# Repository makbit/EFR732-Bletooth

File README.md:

# EFR732-Bluetooth
EFR732 - is a multi-protocol radio board based on the [EFR32MG1P732F256GM32 @40MHz MCU](https://www.silabs.com/wireless/zigbee/efr32mg1-series-1-socs/device.efr32mg1p732f256gm32) from the SiliconLabs in the 5x5mm QFN32 package. Now this MCU is announced as deprecated. :disappointed:

This MCU supports:
* Bluetooth Smart (BLE),
* ZigBee,
* Thread,
* Proprietary protocols.

Maximum TX Power is: 2.4 GHz @ 19.5 dBm, Antenna in the SMA connector adds +3dBm.
This MCU integrate a 512kB serial flash in the package.

### Key features:
 - The board has JTAG/SWD pins compatible with the J-Link debug adapter (PF0 - SWCLK, PF1 - SWDIO, PF2 - SWO).
 - The on-board microphone with the amplifier is connected to the MCU ADC port (PB13).
 - The iDAC output is amplified with the LM321 (PB12).
 - There is a USB-to-UART bridge based on the [EFM8UB31F40 MCU](https://www.silabs.com/mcu/8-bit/efm8-universal-bee/device.efm8ub31f40g-qsop24) : P04_TX -> PA1_RX, P05_RX -> PA0_TX. I hope this 8051 MCU can be used as a programmer/debugger someday.
 - Two pins are connected: P03 -> PB11 (clk), P06 -> PD13 (cs). Debug pins are not connected yet.
 - User push-button is connected to PF3.

The [`Hardware`](Hardware) folder contains Eagle CAD 9.0 schematics files. Component library can be found in my repositories.
The board schematics can be found in the[`Hardware/EFR732.png`](Hardware/EFR732.png) file.

### TODO
- [ ] Add firmware folder with examples and some useful stuff.
- [ ] Write USB-to-UART firmware for EFM8.

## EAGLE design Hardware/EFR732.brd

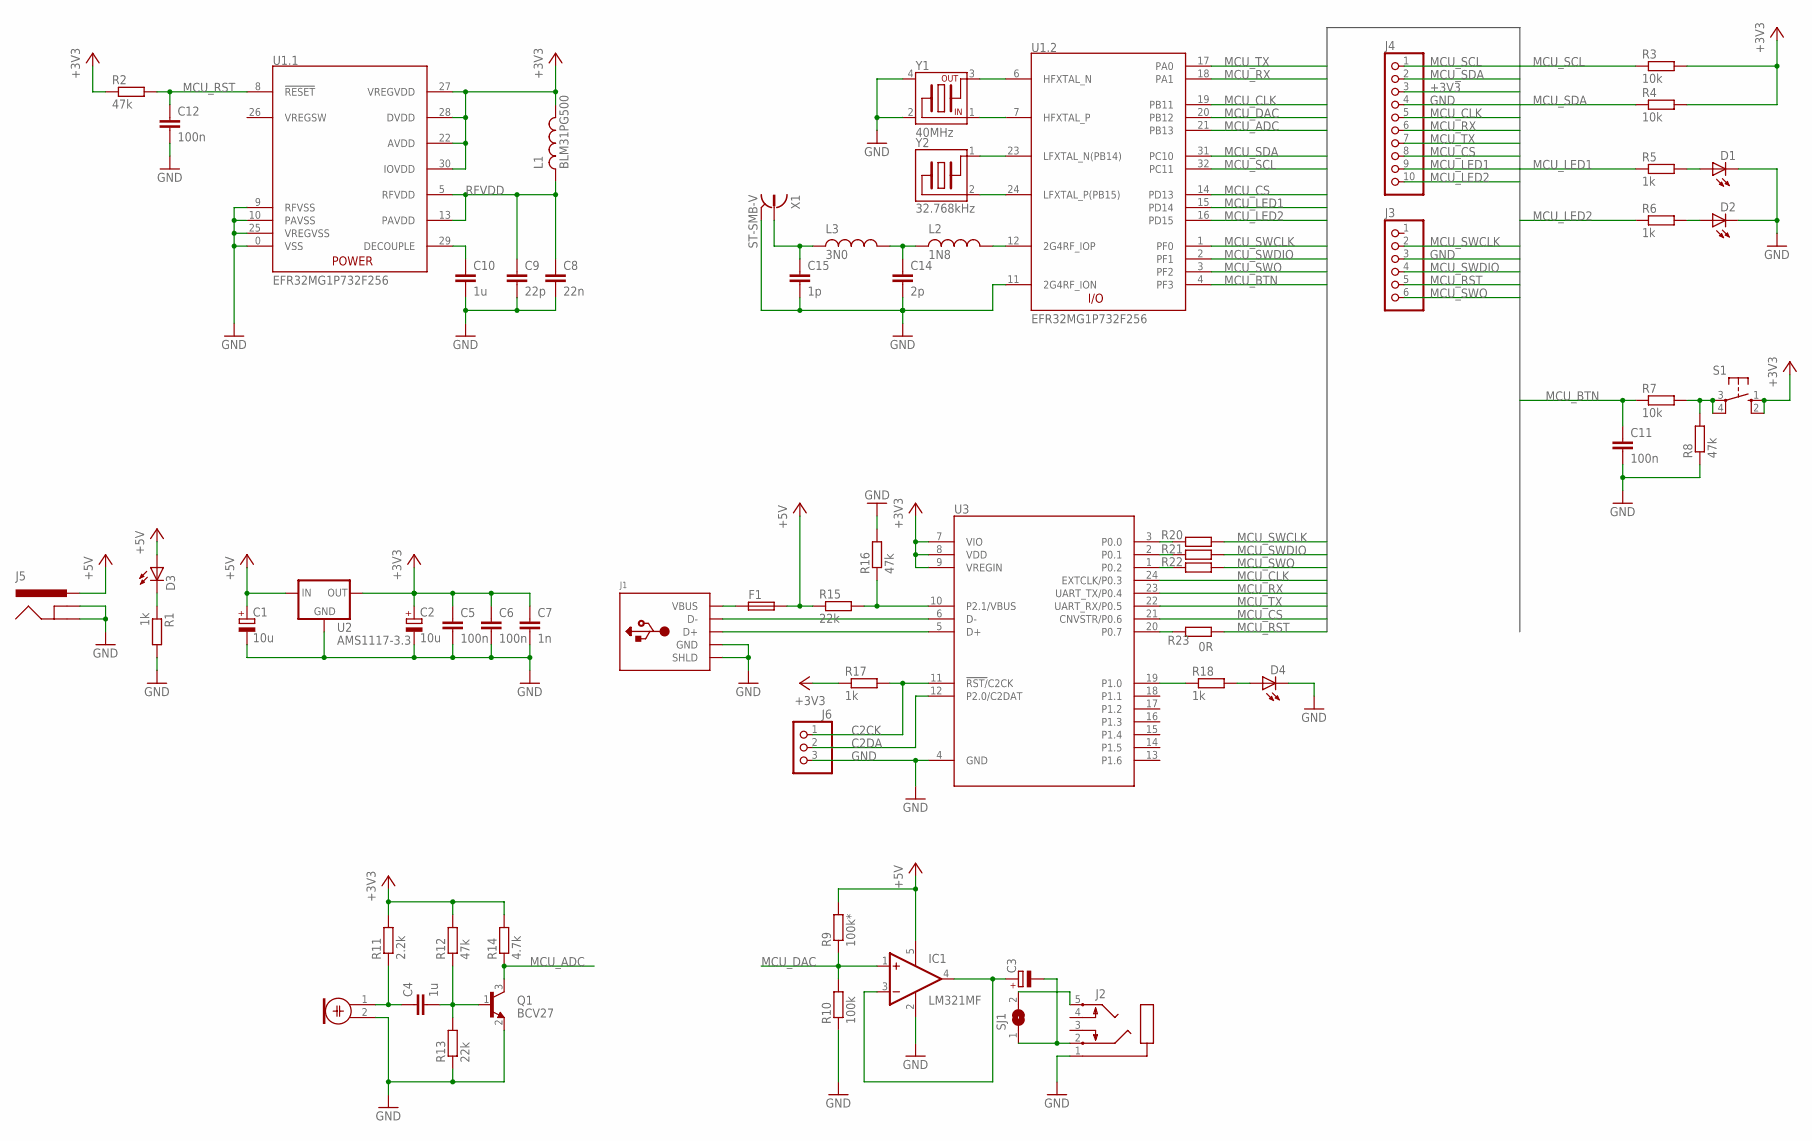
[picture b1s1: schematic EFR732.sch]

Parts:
C1, C2: 10u; RCL-1206F-POL
C3: CPOL-EU; RCL-1206F-POL
C4, C10: 1u; RCL-1206F
C5, C6, C11, C12: 100n; RCL-0805F
C7: 1n; RCL-0805F
C8: 22n; RCL-0805F
C9: 22p; RCL-0805F
C14: 2p; RCL-0805F
C15: 1p; RCL-0805F
D1, D2, D3, D4: LED1206; LED-1206F
F1: FUSE-NSMF; RCL-1206F
IC1: LM321MF; SOT23-5
J1: USB-TYPE-B; USB-TYPE-B-4P
J2: AUDIO-JACK-3.5MM; AUDIO-PG203J
J3: PINH-1X06
J4: PINH-1X10
J5: POWER_JACK; POWER_JACK_PTH
J6: PINHD-1X3; 1X03
L1: BLM31PG500; RCL-1206F
L2: 1N8; RCL-0603F
L3: 3N0; RCL-0603F
M1: ELECTRET_MICROPHON-WM-62PC/62PK; WM-62PC/62PK
Q1: BCV27; SOT23
R1, R5, R6, R17, R18: 1k; RCL-0805F
R2, R8, R12, R16: 47k; RCL-0805F
R3, R4, R7: 10k; RCL-0805F
R9: 100k*; RCL-0805F
R10: 100k; RCL-0805F
R11: 2.2k; RCL-0805F
R13, R15: 22k; RCL-0805F
R14: 4.7k; RCL-0805F
R20, R21, R22: R-EU0805; RCL-0805F
R23: 0R; RCL-0805F
S1: SWITCH-10-XX; BUTTON-B3F-10XX
SJ1: SJ
U1: EFR32MG1P732F256; QFN32_5X5MM_EFR32MG1
U2: AMS1117-3.3; SOT223
U3: EFM8UB31F40G-QSOP24; QSOP24-3.9X8.65MM
X1: ST-SMB-V
Y1: 40MHz; XTAL-FA-238
Y2: 32.768kHz; XTAL-FC-135

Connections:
+3V3: C2.+, C5.1, C6.1, C7.1, J4.3, L1.2, R2.1, R3.2, R4.2, R11.2, R12.2, R14.2, R17.1, S1.1 (S), S1.2 (S1), U1.22 (AVDD), U1.27 (VREGVDD), U1.28 (DVDD), U1.30 (IOVDD), U2.2 (OUT), U2.4 (OUT), U3.7 (VIO), U3.8 (VDD), U3.9 (VREGIN)
+5V: C1.+, D3.A, F1.2, IC1.5 (V+), J5.PWR, R9.2, R15.1, U2.3 (IN)
C2CK: J6.1, R17.2, U3.11 (!RST/!C2CK)
C2DA: J6.2, U3.12 (P2.0/C2DAT)
GND: C1.-, C2.-, C5.2, C6.2, C7.2, C8.2, C9.2, C10.2, C11.2, C12.2, C14.2, C15.2, D1.C, D2.C, D4.C, IC1.2 (V-), J1.4_GND (GND), J1.M1 (SHLD), J1.M2 (SHLD), J2.1, J3.3, J4.4, J5.GND, J5.GNDBREAK, J6.3, M1.2, Q1.2 (E), R1.2, R8.1, R10.1, R13.1, R16.2, U1.0 (VSS), U1.9 (RFVSS), U1.10 (PAVSS), U1.11 (2G4RF_ION), U1.25 (VREGVSS), U2.1 (GND), U3.4 (GND), X1.2, X1.3 (2), X1.4 (2), X1.5 (2), Y1.2, Y1.4
MCU_ADC: Q1.3 (C), R14.1, U1.21 (PB13)
MCU_BTN: C11.1, R7.1, U1.4 (PF3)
MCU_CLK: J4.5, U1.19 (PB11), U3.24 (EXTCLK/P0.3)
MCU_CS: J4.8, U1.14 (PD13), U3.21 (CNVSTR/P0.6)
MCU_DAC: IC1.1 (+IN), R9.1, R10.2, U1.20 (PB12)
MCU_LED1: J4.9, R5.1, U1.15 (PD14)
MCU_LED2: J4.10, R6.1, U1.16 (PD15)
MCU_RST: C12.1, J3.5, R2.2, R23.2, U1.8 (!RESET)
MCU_RX: J4.6, U1.18 (PA1), U3.23 (UART_TX/P0.4)
MCU_SCL: J4.1, R3.1, U1.32 (PC11)
MCU_SDA: J4.2, R4.1, U1.31 (PC10)
MCU_SWCLK: J3.2, R20.2, U1.1 (PF0)
MCU_SWDIO: J3.4, R21.2, U1.2 (PF1)
MCU_SWO: J3.6, R22.2, U1.3 (PF2)
MCU_TX: J4.7, U1.17 (PA0), U3.22 (UART_RX/P0.5)
unnamed: U1.23 (LFXTAL_N(PB14)), Y2.1 (1.XIN)
unnamed: U1.24 (LFXTAL_P(PB15)), Y2.2 (2.XIN)
unnamed: U1.7 (HFXTAL_P), Y1.1 (X.IN)
unnamed: U1.6 (HFXTAL_N), Y1.3 (X.OUT)
unnamed: F1.1, J1.1_VBUS (VBUS)
unnamed: C14.1, L2.1, L3.2
unnamed: R20.1, U3.3 (P0.0)
unnamed: C15.1, L3.1, X1.1
unnamed: D3.C, R1.1
unnamed: D1.A, R5.2
unnamed: C10.1, U1.29 (DECOUPLE)
unnamed: D2.A, R6.2
unnamed: C3.+, IC1.3 (-IN), IC1.4 (OUT)
unnamed: J2.5, SJ1.2
unnamed: R7.2, R8.2, S1.3, S1.4 (P1)
unnamed: J1.2_DM (D-), U3.6 (D-)
unnamed: J1.3_DP (D+), U3.5 (D+)
unnamed: R21.1, U3.2 (P0.1)
unnamed: R15.2, R16.1, U3.10 (P2.1/VBUS)
unnamed: C4.1, M1.1, R11.1
unnamed: C3.-, J2.2, SJ1.1
unnamed: C4.2, Q1.1 (B), R12.1, R13.2
unnamed: R22.1, U3.1 (P0.2)
unnamed: R18.1, U3.19 (P1.0)
unnamed: D4.A, R18.2
unnamed: R23.1, U3.20 (P0.7)
RFVDD: C8.1, C9.1, L1.1, U1.5 (RFVDD), U1.13 (PAVDD)
RF_IOP: L2.2, U1.12 (2G4RF_IOP)
VREGSW: U1.26 (VREGSW)

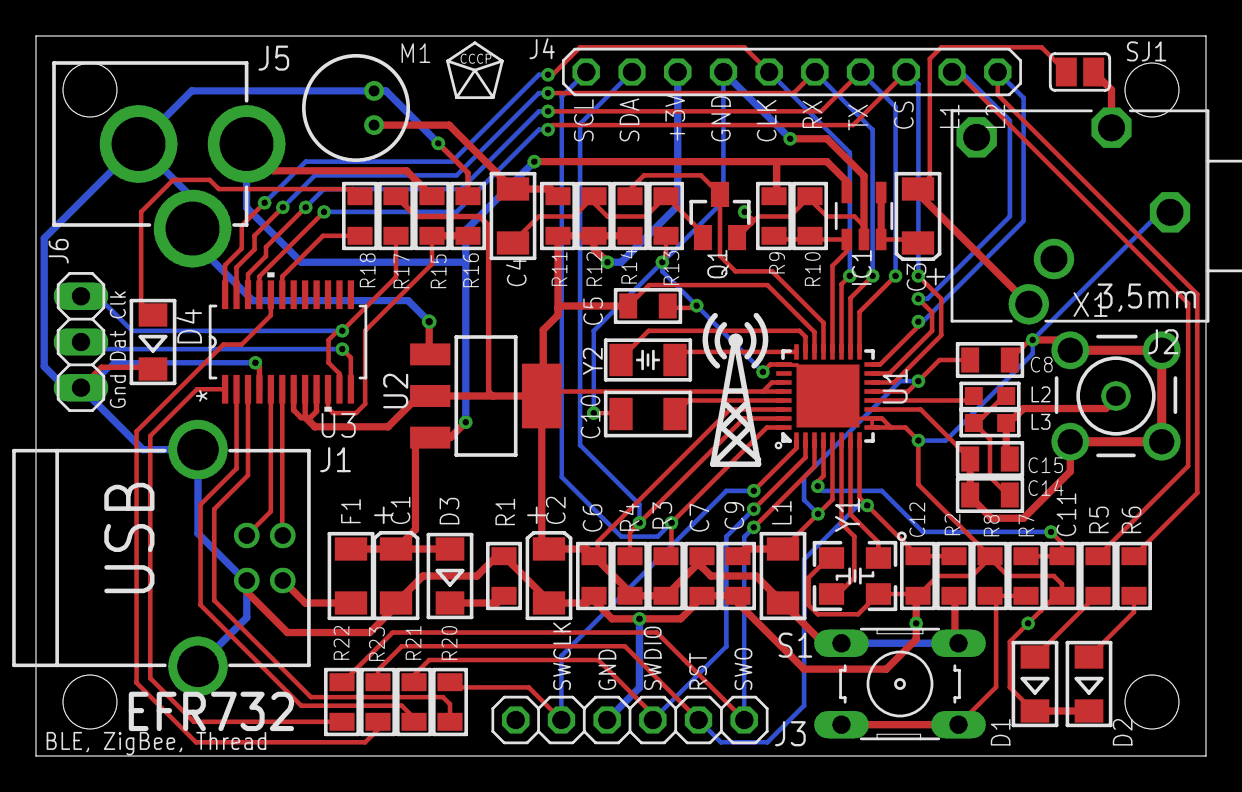
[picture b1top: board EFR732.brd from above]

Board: 2 copper layers, 65.0 x 40.0 mm, 61 parts (0 on the bottom side), 48 nets.

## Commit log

2021-01-18 Hardware project files for Eagle CAD 9.0
2021-01-18 Board image with antenna
2021-01-18 PCB Image with Antenna
